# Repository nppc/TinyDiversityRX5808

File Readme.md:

# Tiny 5.8GHz Diversity VRX for EV100 Goggles
Sample video, showing diversity in work (for example at 1:42).

Recording taken with [Eachine Pro DVR integrated in to the EV100 goggles](https://github.com/nppc/VideoSwitchDVR).

3D rendering of the board:

PCB can be ordered here: https://oshpark.com/shared_projects/An2v0djk

## Proof of concept
- Diversity bench test: https://www.youtube.com/watch?v=jwpYg-zWEIs
- Band/channel change and auto-search test: https://www.youtube.com/watch?v=jH8NeLfK5f4

## Calibration
- Power OFF VTX.
- Power ON Goggles and then press button on tVRX.
- LEDs will make 5 short (100ms) blinks indicating, that lowest video signal detection in progress.
- When LEDs will stay lit, then power ON VTX.
- After about 2 seconds LEDs will make 5 long (900ms) blinks indicating that highest video signal detection in progress.
- When LEDs turn OFF for 2 seconds, then Calibration is done.
- Now tVRX will exit from Calibration mode and go to normal state.

## Compiling
Use latest Arduino IDE.
You need to add ATtiny Support to Arduino IDE (Google the Internet). :)
In Arduino IDE Clock should be left as default = 1MHz (internal).
In this project we don't use Arduino bootloader. So, you need to export compiled binary from IDE and flash it with external programmer like USBasp.
Programming pads on tVRX:

All fuses leave default.

Discussion on RCG: https://www.rcgroups.com/forums/showthread.php?3051872-DIY-Tiny-Diversity-VRX-for-EV100-Goggles

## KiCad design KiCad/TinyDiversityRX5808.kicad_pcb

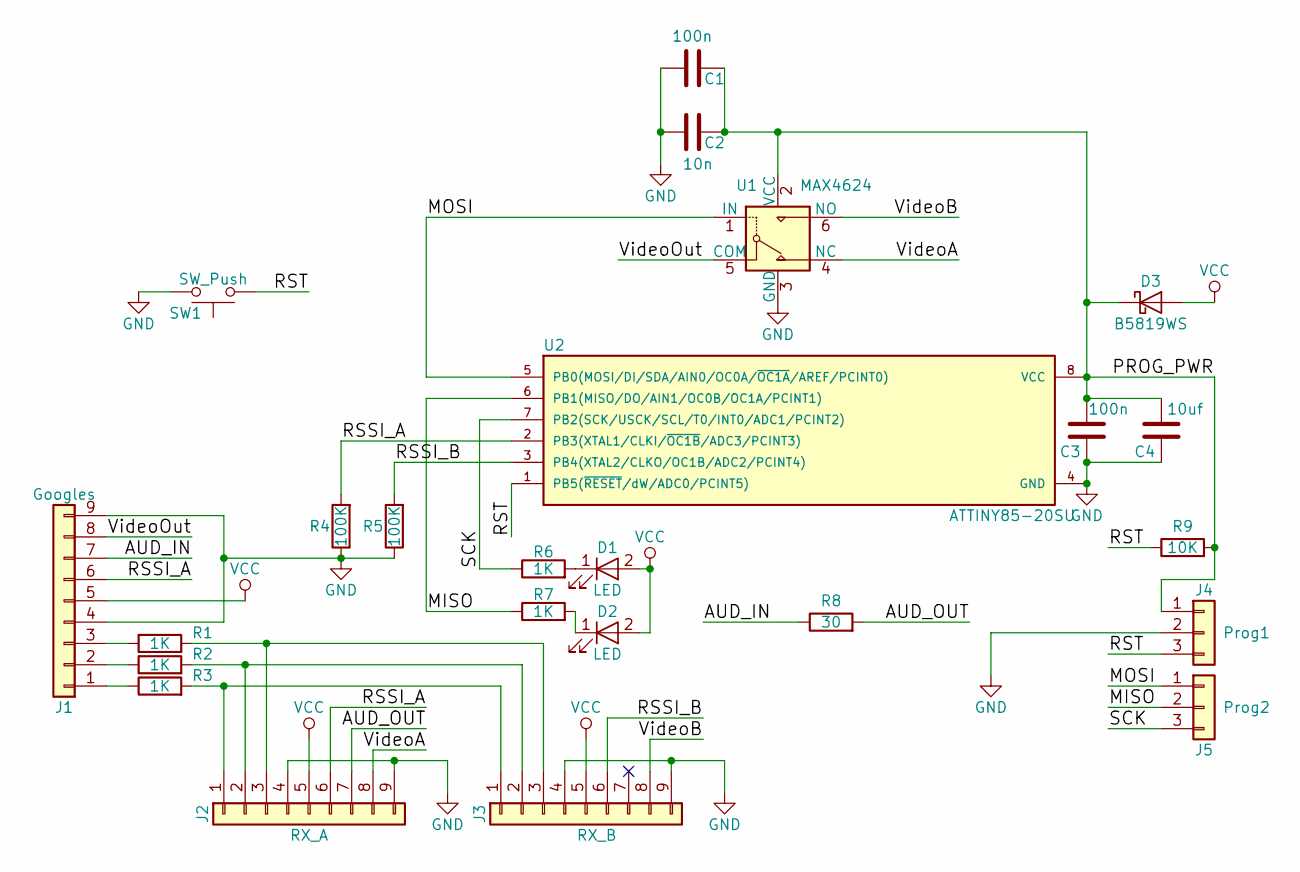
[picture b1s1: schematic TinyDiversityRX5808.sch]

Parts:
C1, C3: 100n; C_0603
C2: 10n; C_0603
C4: 10uf; C_0603
D1, D2: LED; LED_0805
D3: B5819WS; D_SOD-323
J1: Googles; Molex_PicoBlade_53047-0910_09x1.25mm_Straight
J2: RX_A; Molex_PicoBlade_53048-0910_09x1.25mm_Angled
J3: RX_B; Molex_PicoBlade_53048-0910_09x1.25mm_Angled
J4: Prog1; Pads_prog_3pin1.25mm
J5: Prog2; Pads_prog_3pin1.25mm
R1, R2, R3, R6, R7: 1K; R_0603
R4, R5: 100K; R_0603
R8: 30; R_0603
R9: 10K; R_0603
SW1: SW_Push; Button_TS-018
U1: MAX4624; SOT-23-6
U2: ATTINY85-20SU; SOIJ-8_5.3x5.3mm_Pitch1.27mm

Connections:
/AUD_IN: J1.7, R8.1
/AUD_OUT: J2.7, R8.2
/MISO: J5.2, R7.1, U2.6 (PB1(MISO/DO/AIN1/OC0B/OC1A/PCINT1))
/MOSI: J5.1, U1.1 (IN), U2.5 (PB0(MOSI/DI/SDA/AIN0/OC0A/~OC1A~/AREF/P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)
/PROG_PWR: C1.1, C2.1, C3.2, C4.2, D3.1 (K), J4.1, R9.2, U1.2 (VCC), U2.8 (VCC)
/RSSI_A: J1.6, J2.6, R4.2, U2.2 (PB3(XTAL1/CLKI/~OC1B~/ADC3/PCINT3))
/RSSI_B: J3.6, R5.2, U2.3 (PB4(XTAL2/CLKO/OC1B/ADC2/PCINT4))
/RST: J4.3, R9.1, SW1.1, U2.1 (PB5(~RESET~/dW/ADC0/PCINT5))
/SCK: J5.3, R6.1, U2.7 (PB2(SCK/USCK/SCL/T0/INT0/ADC1/PCINT2))
/VideoA: J2.8, U1.4 (NC)
/VideoB: J3.8, U1.6 (NO)
/VideoOut: J1.8, U1.5 (COM)
GND: C1.2, C2.2, C3.1, C4.1, J1.4, J1.9, J2.4, J2.9, J3.4, J3.9, J4.2, R4.1, R5.1, SW1.2, U1.3 (GND), U2.4 (GND)
unnamed 13: D1.1 (K), R6.2; also elsewhere on the board
unnamed 14: D2.1 (K), R7.2; also elsewhere on the board
unnamed: J1.1, R3.1
unnamed: J1.2, R2.1
unnamed: J1.3, R1.1
unnamed: J2.1, J3.1, R3.2
unnamed: J2.2, J3.2, R2.2
unnamed: J2.3, J3.3, R1.2
VCC: D1.2 (A), D2.2 (A), D3.2 (A), J1.5, J2.5, J3.5; also elsewhere on the board

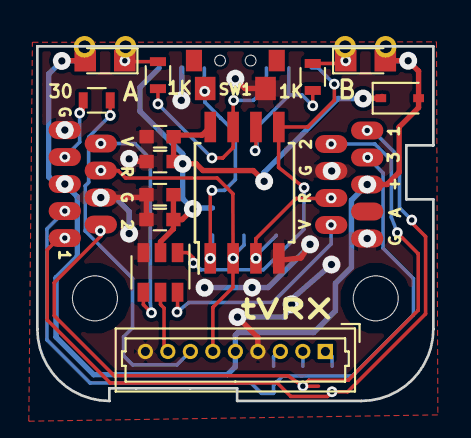
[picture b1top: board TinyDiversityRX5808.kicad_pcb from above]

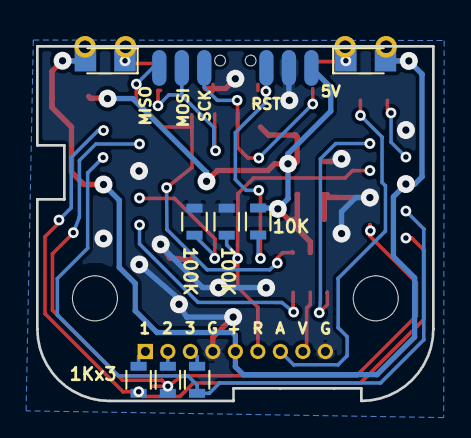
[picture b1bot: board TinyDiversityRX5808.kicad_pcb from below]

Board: 2 copper layers, 22.0 x 19.7 mm, 26 parts (10 on the bottom side), 22 nets.

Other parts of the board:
D1#2, D2#2: LED; LED_0805

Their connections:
unnamed 13: D1#2.1; also elsewhere on the board
unnamed 14: D2#2.1; also elsewhere on the board
VCC: D1#2.2, D2#2.2; also elsewhere on the board

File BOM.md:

## Bill of Materials

Ref | Value | size/footprint
-------- | ---------------- | ----------
U1 | MAX4624 | SOT-23-6
U2 | ATTINY25, ATTINY45 or ATTINY85 | SOIC8
R1,R2,R3 | 1K | 0603
R4,R5 | 100K | 0603
R6,R7 | 560-1K | 0603
R8 | 30 | 0603
R9 | 10K | 0603
C1, C3 | 100n | 0603
C2 | 10n | 0603
C4 | 10uf | 0603
D1,D2 | LED | 0805
D3 | B5819WS (or any) | SOD-323
Button | 6mm X 7.3mm | https://www.banggood.com/50Pcs-2x4x3_5mm-Tact-Tactile-Push-B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

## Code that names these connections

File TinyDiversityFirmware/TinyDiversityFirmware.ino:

//#define DEBUG


#include <EEPROM.h>

//#define MIN_TUNE_TIME 25 // update RSSI values every 25ms

// RSSI strength should be greater than the value below (percent) over the
// other receiver before we switch. This prevents flicker when RSSI values
// are close
#define DIVERSITY_HYSTERESIS 2

// How long (ms) the RSSI strength has to have a greater difference than the
// above before switching.
#define DIVERSITY_HYSTERESIS_PERIOD 100

// Calibration for Max RSSI value will start 
// after the RSSI ADC value will be higher than 
// min RSSI ADC value plus CALIBRATION_ADC_DIFFERENCE.
#define CALIBRATION_ADC_DIFFERENCE 100


#define PIN_SWITCH_VIDEO 	0	//PB0
#define PIN_LED_A 			2 	//PB2
#define PIN_LED_B 			1	//PB1
#define PIN_RSSI_A 			A3	//PB3
#define PIN_RSSI_B 			A2	//PB4

// don't use first byte of EEPROM. It can be corrupted
#define EEPROM_RESET_FLAG_ADDR	5	// RESET Flag (byte)
#define EEPROM_MIN_RSSI_A_ADDR	7	// RSSI RAW Calibration value (int)
#define EEPROM_MAX_RSSI_A_ADDR	9	// RSSI RAW Calibration value (int)
#define EEPROM_MIN_RSSI_B_ADDR	11	// RSSI RAW Calibration value (int)
#define EEPROM_MAX_RSSI_B_ADDR	13	// RSSI RAW Calibration value (int)

#define INTERNAL2V56_NO_CAP (6)

uint8_t activeReceiver;
uint8_t diversityTargetReceiver;

typedef struct {
  int min;
  int max;
  int raw;
  uint8_t mapped;
} RSSI;

RSSI rssiA;
RSSI rssiB;

unsigned long diversityHysteresisTimer;


enum ReceiverSelect: byte {RX_A, RX_B};

// some macros
#define LED_A_ON bitClear(PORTB, PIN_LED_A) // LED A ON
#define LED_B_ON bitClear(PORTB, PIN_LED_B) // LED B ON
#define LED_A_OFF bitSet(PORTB, PIN_LED_A) // LED A OFF
#define LED_B_OFF bitSet(PORTB, PIN_LED_B) // LED B OFF


void setupPins() {
	bitSet(DDRB, PIN_SWITCH_VIDEO);
	bitSet(DDRB, PIN_LED_A);
	bitSet(DDRB, PIN_LED_B);
	LED_A_OFF;
	LED_B_OFF;
}

void setup()
{
	// First lets read RESET Flag; Power (bit0), Reset (bit 1), etc
	uint8_t RESET_value = MCUSR;
	MCUSR = 0;	// reset flag for nect use
	
	//analogReference(INTERNAL2V56_NO_CAP);
	analogReference(INTERNAL);	// 1.1v
	
	setupPins();

	uint8_t last_RESET_value = EEPROM.read(EEPROM_RESET_FLAG_ADDR);
	EEPROM.update(EEPROM_RESET_FLAG_ADDR, RESET_value);	// Only update if value is changed

	// should we enter calibration mode
	if(bitRead(last_RESET_value,1)!=1 && bitRead(RESET_value,1)==1){
		// enter Calibration Mode
		doCalibration();
		EEPROM.update(EEPROM_RESET_FLAG_ADDR, 1); //clear RESET flag to enter calibration mode after new RESET
	}
	// should we abort calibration mode
	if(bitRead(last_RESET_value,1)==1 && bitRead(RESET_value,1)==1){
		// abort Calibration Mode
		EEPROM.update(EEPROM_RESET_FLAG_ADDR, 1); //clear RESET flag to enter calibration mode after new RESET
	}

    setActiveReceiver(RX_A);
	diversityTargetReceiver = activeReceiver;	// Initialize variable for diversity switching
	
	readEEPROMSettings();
	updateRssi();	// Initialize variables

}

void setActiveReceiver(ReceiverSelect Set_RX){
	activeReceiver = Set_RX;
	if(activeReceiver == RX_A){
		bitClear(PORTB, PIN_SWITCH_VIDEO);
		LED_A_ON;
		LED_B_OFF;
	}else{
		bitSet(PORTB, PIN_SWITCH_VIDEO);
		LED_A_OFF;
		LED_B_ON;
	}
}

uint8_t remapRawRssiValue(RSSI rssi) {
  return constrain(map(rssi.raw, rssi.min, rssi.max, 0, 100), 0, 100);
}

void updateRssi() {
	analogRead(PIN_RSSI_A); // Fake read to let ADC settle.
	rssiA.raw = analogRead(PIN_RSSI_A);
	rssiA.mapped = remapRawRssiValue(rssiA);
 
	analogRead(PIN_RSSI_B); // Fake read to let ADC settle.
	rssiB.raw = analogRead(PIN_RSSI_B);
	rssiB.mapped = remapRawRssiValue(rssiB);
}
	
void switchDiversity() {

	int8_t rssiDiff = (int8_t) rssiA.mapped - (int8_t) rssiB.mapped;
	uint8_t rssiDiffAbs = abs(rssiDiff);
	uint8_t currentBestReceiver;
	uint8_t nextReceiver;
	
	nextReceiver = activeReceiver;

	if (rssiDiff > 0) {
		currentBestReceiver = RX_A;
	} else if (rssiDiff < 0) {
		currentBestReceiver = RX_B;
	} else {
		currentBestReceiver = activeReceiver;
	}

	if (rssiDiffAbs >= DIVERSITY_HYSTERESIS) {
		if (currentBestReceiver == diversityTargetReceiver) {
			if ((diversityHysteresisTimer+DIVERSITY_HYSTERESIS_PERIOD)<millis()) {
				nextReceiver = diversityTargetReceiver;
			}
		} else {
			diversityTargetReceiver = currentBestReceiver;
			diversityHysteresisTimer=millis();
		}
	} else {
		diversityHysteresisTimer=millis();
	}

	setActiveReceiver(nextReceiver);

}
	
void loop() {
    // Update RSSI values as fast as possible.
	updateRssi();
	switchDiversity(); // Will switch only if signals are significantly different and difference stays for a while.
}

void readEEPROMSettings(){
	rssiA.min=readEEPROMint(EEPROM_MIN_RSSI_A_ADDR);
	rssiA.max=readEEPROMint(EEPROM_MAX_RSSI_A_ADDR);
	rssiB.min=readEEPROMint(EEPROM_MIN_RSSI_B_ADDR);
	rssiB.max=readEEPROMint(EEPROM_MAX_RSSI_B_ADDR);
}

int readEEPROMint(uint8_t addr){
	return EEPROM.read(addr)+EEPROM.read(addr+1)*256;
}

void writeEEPROMint(uint8_t addr, uint16_t value){
	EEPROM.update(addr, lowByte(value));
	EEPROM.update(addr+1, highByte(value));
}

void doCalibration(){

#if defined(DEBUG)
	// switch video source every 4 seconds in DEBUG mode
	while(1==1){
		mDelay(4000);
		setActiveReceiver(RX_A);
		mDelay(4000);
		setActiveReceiver(RX_B);

/*
		// show ADC values divided by 20.
		int tmp;
		mDelay(2000);
		LED_A_ON;
		LED_B_ON;
		mDelay(700);
		LED_A_OFF;
		LED_B_OFF;
		mDelay(2000);
		updateRssi();
		tmp = rssiA.raw / 64;
		for(int i=0;i<tmp;i++){
			LED_A_ON;
			mDelay(100);
			LED_A_OFF;
			mDelay(400);
		}
		mDelay(2000);
		updateRssi();
		tmp = rssiB.raw / 64;
		for(int i=0;i<tmp;i++){
			LED_B_ON;
			mDelay(100);
			LED_B_OFF;
			mDelay(400);
		}
*/
	}

#else
	// Calibration routine
	// 1. Wait for lowest RSSI while some period (short blinks). Record min value.
	// 2. Now LEDs are ON. Wait for VTX powered ON. 
	// 3. If RSSI changed dramatically, then wait 2 seconds (LEDs are ON).
	// 4. Wait for highest RSSI while some period (long blinks). Record max value.
	// 5. Store calibration data in EEPROM (LEDs are OFF).
	unsigned long tmr_tmp;
	int curMinRSSIA=1023; // max 10 bit ADC value is 1023
	int curMinRSSIB=1023; // max 10 bit ADC value is 1023
	int curMaxRSSIA=0;
	int curMaxRSSIB=0;
	// 5 short blinks for capturing low signal
	for(uint8_t i=0;i<5;i++){
		LED_A_ON;
		LED_B_ON;
		mDelay(100);
		LED_A_OFF;
		LED_B_OFF;
		tmr_tmp = millis();
		while((tmr_tmp+700)>millis()){
			updateRssi();	// refresh RSSI RAW values
			if(rssiA.raw<curMinRSSIA)curMinRSSIA = rssiA.raw;
			if(rssiB.raw<curMinRSSIB)curMinRSSIB = rssiB.raw;
		}
	}
	// Now wait until RSSI will jump for a good degree (CALIBRATION_ADC_DIFFERENCE ADC values) for both receivers
	LED_A_ON;
	LED_B_ON;
	while((rssiA.raw<curMinRSSIA+CALIBRATION_ADC_DIFFERENCE) || (rssiB.raw<curMinRSSIB+CALIBRATION_ADC_DIFFERENCE)){
		mDelay(100);
		updateRssi();
	}
	mDelay(2000); // Delay for 2 seconds for VTX stabilize
	// 5 long blinks for capturing high signal
	for(uint8_t i=0;i<5;i++){
		LED_A_ON;
		LED_B_ON;
		tmr_tmp = millis();
		while((tmr_tmp+900)>millis()){
			updateRssi();	// refresh RSSI RAW values
			if(rssiA.raw>curMaxRSSIA)curMaxRSSIA = rssiA.raw;
			if(rssiB.raw>curMaxRSSIB)curMaxRSSIB = rssiB.raw;
		}
		LED_A_OFF;
		LED_B_OFF;
		mDelay(100);
	}
	// Now it is time to store values to EEPROM
	writeEEPROMint(EEPROM_MIN_RSSI_A_ADDR,curMinRSSIA);
	writeEEPROMint(EEPROM_MAX_RSSI_A_ADDR,curMaxRSSIA);
	writeEEPROMint(EEPROM_MIN_RSSI_B_ADDR,curMinRSSIB);
	writeEEPROMint(EEPROM_MAX_RSSI_B_ADDR,curMaxRSSIB);
	mDelay(2000);	// wait before exit from Calibration

#endif
}

void mDelay(int dtmp){
	unsigned long tmp = millis();
	while((tmp+dtmp)>millis()){}
}

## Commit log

2017-11-16 Prototype board is ready
2017-11-17 Reworked PCB with larger gaps
2017-11-17 thicker thermals
2017-11-17 Mask pdf is inverted
2017-11-20 Initial writeup on firmware
2017-11-21 Added signal switching routine
2017-11-21 Draft of final version
2017-11-21 Slight code optimization
2017-11-21 Slight code optimization (93%)
2017-11-21 Slight code optimization (92%)
2017-11-22 RSSI code optimisation
2017-11-22 Typo corrected
2017-12-04 Modified test board
2017-12-05 Second version of prototype board is ready
2017-12-05 Slight asjustment to the PCB
2017-12-05 Change firmware for V2 board
2017-12-06 Remove outdated files
2017-12-07 BOM for prototype added
2017-12-07 Added schottky value
2017-12-16 Added debug compiled hex
2017-12-20 First draft of final PCB
2017-12-20 Changed attiny case from QFN to SOIC8
2017-12-20 Ready for production version
2017-12-21 Adjusted holes distance
2017-12-22 Changed via drill size to 0.3mm
2018-01-17 Moved 30 ohm resistor
2018-01-28 hex and image added
2018-03-14 Some debug code added
2018-03-14 Working alfa version
2018-03-14 Working beta version. Better hysteresis values
2018-03-15 Added Readme and slightly adjusted calibratin routine
2018-03-18 Rename files. Slight adjust to the readme.
2018-03-19 Added some images
2018-03-19 Added some more photos of PCB and EV100 assembling
2018-03-19 BOM adjusted. PCB 3d model images
2018-03-19 Restored holes for LEDs side soldering
2018-03-19 Button URL added
2018-03-19 Added circuit diagram
2018-03-19 Added PDF circuit diagram
2018-03-20 Misprint fixed
2018-03-20 Small typo adjustments
2018-03-20 add video switch datasheet
2018-03-21 Change schottky footprint
2018-03-21 Adjust link to OSHPark latest PCB
2018-03-21 Added compilinf and flashing instructions
2018-03-21 fixed programmer name
2018-05-02 tested and working version
2018-05-03 some comments fixed. Thank you tun0.
2018-05-07 Added video sample
2018-06-18 Layout change for easier solder and more thin design
2018-06-19 Add panelized PCB (4x4)
2018-07-20 hex files added
2018-09-20 Added mouser codes to BOM
2019-05-24 Silk screen correction png
2019-05-24 Adding U1 replacement
    STG719 sems can be used.
